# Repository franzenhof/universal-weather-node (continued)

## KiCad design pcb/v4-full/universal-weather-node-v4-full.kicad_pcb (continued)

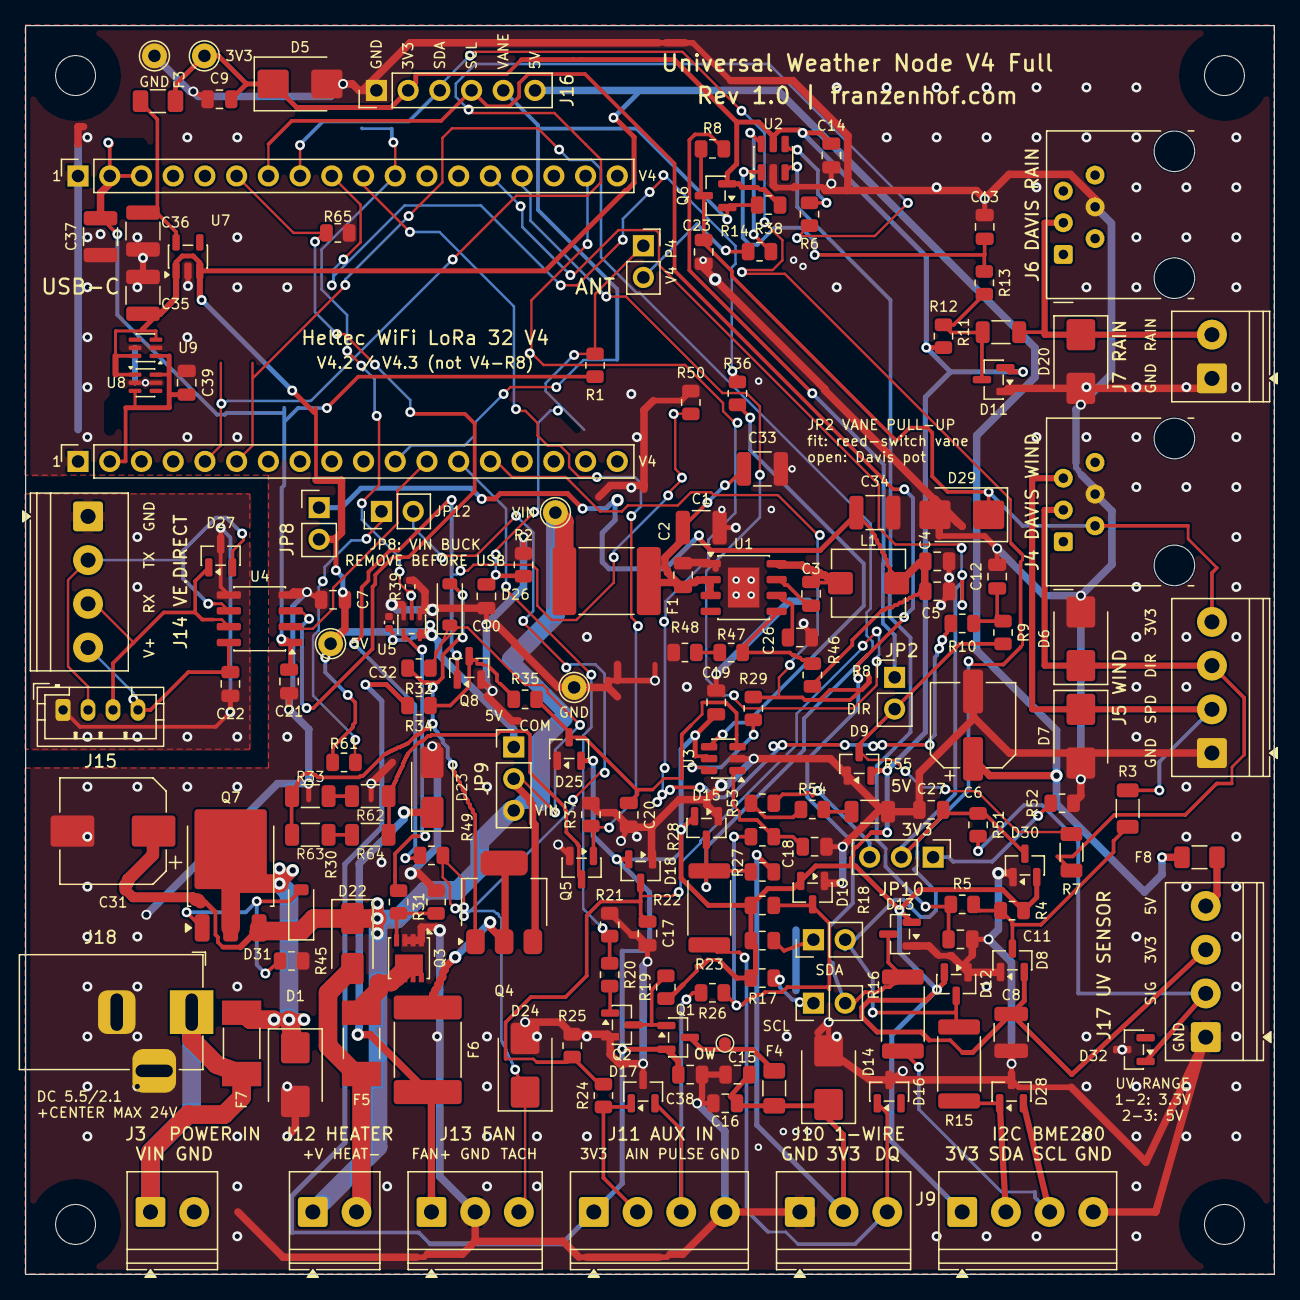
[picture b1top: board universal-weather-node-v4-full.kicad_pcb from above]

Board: 2 copper layers, 100.0 x 100.0 mm, 176 parts (1 on the bottom side), 88 nets.

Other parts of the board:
H1, H2, H3, H4: M3; MountingHole_3.2mm_M3

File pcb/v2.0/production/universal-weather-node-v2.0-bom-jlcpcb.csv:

"Comment","Designator","Footprint","LCSC Part #","MPN"
"10uF 50V","C1,C8,C33,C35,C36","Capacitor_SMD:C_1210_3225Metric","C77102","Murata GRM32ER71H106KA12L (10 uF, 50 V, X7R, 1210)"
"220nF 100V","C2","Capacitor_SMD:C_0805_2012Metric","C513710","Yageo CC0805KKX7R0BB224"
"100nF","C3,C7,C9,C10,C11,C14,C16,C17,C18,C19,C20,C21,C22,C23,C27","Capacitor_SMD:C_0805_2012Metric","C49678","Yageo CC0805KRX7R9BB104"
"22uF 25V","C4,C5,C38","Capacitor_SMD:C_0805_2012Metric","C45783","Samsung CL21A226MAQNNNE (22 uF, 25 V, X5R, 0805; basic)"
"100uF","C6","Capacitor_SMD:CP_Elec_6.3x7.7","C970685","DMBJ RVT1E101M0607 (25V)"
"1uF 50V","C12,C13,C15,C26,C39","Capacitor_SMD:C_0805_2012Metric","C28323","Samsung CL21B105KBFNNNE (1 uF 50 V X7R)"
"47uF 63V","C31","Capacitor_SMD:CP_Elec_8x10","C445452","Nichicon UCD1J470MNL1GS (47 uF, 63 V, SMD 8x10 mm)"
"100nF","C32","Capacitor_SMD:C_0402_1005Metric","C1525","Samsung CL05B104KO5NNNC (100 nF, 16 V, X7R, 0402)"
"22uF 25V","C34,C37","Capacitor_SMD:C_1210_3225Metric","C21397","Murata GRM32ER71E226KE15L (22 uF, 25 V, X7R, 1210)"
"SMBJ30CA","D1","Diode_SMD:D_SMB","C83847","Littelfuse SMBJ30CA"
"SMLVT3V3","D5,D6,D7,D14,D20,D29","Diode_SMD:D_SMB","C283619","SMLVT3V3"
"BAT54S","D8,D9,D11,D12,D13,D15,D18,D19,D25,D30","Package_TO_SOT_SMD:SOT-23","C7420333","R+O BAT54S (series pair, SOT-23; preferred extended)"
"PESD5V0S2BT","D16,D17,D27,D28,D32","Package_TO_SOT_SMD:SOT-23","C49338","Nexperia PESD5V0S2BT,215"
"SS210","D22,D23","Diode_SMD:D_SMA","C14996","SS210 (2 A, 100 V Schottky, SMA; basic)"
"SMBJ33A","D24","Diode_SMD:D_SMB","C19077586","SMBJ33A (33 V standoff, unidirectional, SMB; preferred extended)"
"BZT52C12","D26,D31","Diode_SMD:D_SOD-123","C19077410","BZT52C12 (12 V zener, SOD-123; preferred extended)"
"PTC 1.5A 60V","F1,F6","Fuse:Fuse_2920_7451Metric","C19078738","LUTE 2920L150/60GR (1.5 A hold, 60 V)"
"PTC 0.25A","F3","Fuse:Fuse_1206_3216Metric","C70068","nSMD025 (16V)"
"PTC 0.1A","F4,F8","Fuse:Fuse_1206_3216Metric","C70065","nSMD010 (60V)"
"4A 250V","F5","Fuse:Fuse_Littelfuse-NANO2-451_453","C19712551","SETsafe SCT6125T4A250V (4 A, 250 V)"
"6.3A 125V","F7","Fuse:Fuse_Littelfuse-NANO2-451_453","C178982","Littelfuse 045106.3MRL (6.3 A, 125 VDC)"
"10uH","L1","Inductor_SMD:L_Bourns_SRP5030T","C189932","Bourns SRP5030T-100M"
"AO3401A","Q1,Q6","Package_TO_SOT_SMD:SOT-23","C15127","AO3401A"
"AO3400A","Q2","Package_TO_SOT_SMD:SOT-23","C20917","AOS AO3400A"
"AON7264E","Q3","Package_SO:Vishay_PowerPAK_1212-8_Single","C431191","AOS AON7264E (60 V N-MOSFET, DFN 3.3x3.3)"
"DMP6023LE","Q4","Package_TO_SOT_SMD:SOT-223-3_TabPin2","C154901","Diodes Incorporated DMP6023LE-13"
"AO3422","Q5","Package_TO_SOT_SMD:SOT-23","C37130","AOS AO3422 (55 V N-MOSFET)"
"NCE60P50K","Q7","Package_TO_SOT_SMD:TO-252-3_TabPin2","C130104","NCE Power NCE60P50K"
"MMBT3904","Q8","Package_TO_SOT_SMD:SOT-23","C20526","Jiangsu Changjing MMBT3904(RANGE:100-300)"
"1M","R1,R2","Resistor_SMD:R_0805_2012Metric","C17514","UniOhm 0805W8F1004T5E"
"330","R3,R7,R11,R55","Resistor_SMD:R_1206_3216Metric","C17930","UniOhm 1206W4F3300T5E (1206, 0.25 W)"
"4.7k","R4,R5,R8,R12,R17,R18,R22,R27,R28,R35,R54","Resistor_SMD:R_0805_2012Metric","C17673","UniOhm 0805W8F4701T5E"
"1k","R6,R10,R14,R20,R29,R36","Resistor_SMD:R_0805_2012Metric","C17513","UniOhm 0805W8F1001T5E"
"10k","R9,R13,R21,R24,R34,R47,R51,R53,R61","Resistor_SMD:R_0805_2012Metric","C17414","UniOhm 0805W8F1002T5E"
"33 1W","R15,R16,R23","Resistor_SMD:R_2512_6332Metric","C53728","UniOhm 25121WF330JT4E (2512, 1 W)"
"47k","R19,R46,R49","Resistor_SMD:R_0805_2012Metric","C17713","UniOhm 0805W8F4702T5E"
"220","R26,R30","Resistor_SMD:R_0805_2012Metric","C17557","UniOhm 0805W8F2200T5E"
"100k","R31,R37,R38,R45,R50,R52,R65","Resistor_SMD:R_0805_2012Metric","C149504","UniOhm 0805W8F1003T5E"
"75k","R32","Resistor_SMD:R_0805_2012Metric","C17819","UNI-ROYAL 0805W8F7502T5E (75 kOhm, 1%, 0.125 W, 0805)"
"2k","R33,R62,R63,R64","Resistor_SMD:R_1206_3216Metric","C17944","UNI-ROYAL 1206W4F2001T5E (2 kOhm, 1%, 0.25 W, 1206)"
"100k","R39","Resistor_SMD:R_0402_1005Metric","C25741","UniOhm 0402WGF1003TCE"
"1.8k","R48","Resistor_SMD:R_0805_2012Metric","C17398","Uniroyal 0805W8F1801T5E"
"LMR36520ADDAR","U1","Package_SO:SOIC-8-1EP_3.9x4.9mm_P1.27mm_EP2.514x3.2mm","C2879422","TI LMR36520ADDAR"
"SN74LVC2G14DBVR","U2,U3","Package_TO_SOT_SMD:SOT-23-6","C5375976","UMW SN74LVC2G14DBVR (second source; TI C12401 had 33 in stock on 2026-11-21)"
"ADuM121N1BRZ","U4","Package_SO:SOIC-8_3.9x4.9mm_P1.27mm","C190783","ADUM121N1BRZ-RL7 (alt. ISO7721DR C366164)"
"SN74AHCT1G125DCKR","U5","Package_TO_SOT_SMD:SOT-353_SC-70-5","C350557","TI SN74AHCT1G125DCKR (SC-70-5)"
"AP2112K-3.3TRG1","U7","Package_TO_SOT_SMD:SOT-23-5","C51118","Diodes AP2112K-3.3TRG1 (600 mA LDO, SOT-23-5)"
"LM66100DCKR","U8,U9","Package_TO_SOT_SMD:SOT-363_SC-70-6","C2869734","TI LM66100DCKR (ideal diode 1.5 A, 79 mOhm, SC-70-6)"

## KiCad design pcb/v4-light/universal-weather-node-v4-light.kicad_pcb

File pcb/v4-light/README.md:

# Weather Node V4 Light Rev 1.0 (Heltec V4, through-hole)

A hand-solderable, low-cost board for the **Heltec WiFi LoRa 32 V4** (V4.2 / V4.3, not V4-R8).
All parts are through-hole except the TVS diodes: six SMB (large pads, easy to solder by hand) and
two optional PESD5V0S2BT in SOT-23.
It carries the core functions of the **V4 Full** with the **same GPIOs and the same signal
conditioning**:

| Function | Connector | V4 GPIO |
|----------|-----------|---------|
| Davis wind speed / direction | J4 RJ11 + J5 screw terminal (GND, SPD, DIR, 3V3) | 44 / 6 (ADC1) |
| Wind-vane supply (switched, LOW = on) | J4 pin 2 / J5 3V3 | 34 |
| Davis rain | J6 RJ11 + J7 screw terminal (GND, RAIN) | 16 (P4) |
| BME280 (I²C) | J8 (3V3, SDA, SCL, GND) | 41 / 42 |
| DS18B20 (1-Wire), switched supply (HIGH = on) | J9 (GND, 3V3, DQ) | 43 / 47 |
| Hardware revision ID | – | 15 (P4) |

**Power:** the board has no power input of its own. Power and flash the module through its
**USB-C** connector (V4 header pin 2 = USB VBUS stays open, so there is no back-feeding).
The sensors run from the module's 3.3 V through a 170 mA PTC (F1); the 1-Wire supply has its
own 100 mA PTC (F2).

**Not on the V4 Light** (V4 Full only): VIN 6–29 V supply, heater and fan outputs, fan tacho,
AUX inputs, UV input, VE.Direct.

**Board:** 100 × 80 mm, 2 layers, four M3 holes on a 66 × 72 mm pattern (centres 30/96 mm from the
left edge, 4/76 mm from the top). The V4 stands at the left edge, USB-C flush with the top edge.
71 parts (2 of them optional), see the [BOM](production/universal-weather-node-v4-light-bom.csv).

## Protection and conditioning

- **SMB TVS SMLVT3V3** at wind speed, wind direction, rain (between each jack and its terminal),
  the switched vane supply, the 1-Wire supply and the 3.3 V sensor rail.
- **Resistors on a 10.16 mm (400 mil) pitch** like Rev 1.3: room for Vishay PR01 (1 W, 6.5 × 2.5 mm)
  as well as ordinary 0207 / 0204 metal-film parts.
- **330 Ω** series resistors (Davis lines), **100 Ω** (I²C, 1-Wire DQ), **BAT43** clamps to 3.3 V
  and GND on every input.
- **PESD5V0S2BT** (low-capacitance dual ESD TVS, SOT-23) directly at J8 (SDA, SCL) and J9 (DQ) —
  **optional**: leave them out if SOT-23 is too fiddly, the 100 Ω + BAT43 into the TVS-protected
  3.3 V rail remain. An SMB TVS is not used there because its capacitance would load the buses.
- **Mounting holes plated and on GND:** screwed to a grounded metal plate or enclosure, ESD
  discharges take the short way to ground instead of crossing the board.
- RC filters as on the V4 Full (wind speed 4.7k/100 nF, direction 10k/1 µF, rain 10k/1 µF) and a
  **74HC14** (DIP-14) inverting Schmitt trigger for wind speed and rain — the same polarity as the
  V4 Full's 74LVC2G14, so the firmware counts identically.
- JP1: 4.7k pull-up for reed-switch vanes (open for the Davis potentiometer). JP2/JP3: extra 4.7k
  I²C pull-ups for cables longer than 0.5 m.

## Silkscreen

Verbose on purpose: every part carries its value on the front (inside the body outline where it is
free of pads, otherwise beside it — only C3 is printed in the back BOM alone), FET type
(P-FET / N-FET) next to Q1–Q3, terminal pin names, jumper functions. The back carries the complete
BOM grouped by value (resistors, capacitors / fuses, diodes / FET / IC, connectors), the connector
pinouts by pin number, jumpers and GPIOs, and polarity / assembly-order notes
(`tools/pcbgen/light_silk.py`).

## Revision ID and firmware

R1/R2 = 1 MΩ / 470 kΩ put **0.32 × 3.3 V ≈ 1.06 V** on GPIO15 (V4 Full: 1 MΩ / 1 MΩ ≈ 1.65 V,
accepted window 1.30–2.00 V). The firmware (4.x) accepts **0.85–1.25 V as V4 Light** (`pcbRev` 21;
V4 Full stays 20), logs `HW revision ID (GPIO15): … mV -> PCB V4 Light` and offers only the
functions above: heater, fan, tacho, AUX, second wind sensor, UV and VE.Direct are hidden in the
web settings and refused by downlink/MQTT, and their GPIOs are never driven.

## Assembly

1. SMD first: the SMB TVS diodes (band = cathode = pad 1 on the signal side) and, if fitted,
   D19/D20 (PESD5V0S2BT, SOT-23); then the low parts
   (resistors, BAT43 — band = cathode, ceramic capacitors), DIP socket, TO-92, PTCs, C2 (+ = square pad),
   headers, terminals and RJ11 jacks, the Heltec sockets last. The TVS diodes sit 3–5 mm clear of the RJ11 jacks and screw terminals,
   so they can still be soldered if the jacks went in first.
2. **Q1/Q2 (LP0701N3-G) and Q3 (TN2106N3-G) are S-G-D in TO-92 (N3)** (datasheets checked; the SOT-23 versions K1/LG differ) — check the flat side against the
   silkscreen outline.
3. **J3 (P4 socket, GPIO15/16) sits 0.45 mm off the 2.54 mm grid** (position from Heltec's V4 3D model):
   check it with a real V4 before soldering the sockets. Solder J1/J2/J3 with the module plugged in.

## Status

Generated with `tools/pcbgen` (`design_light.py`, `schem_light.py`, `layout_light.py`, then
`light_silk.py` for the verbose silkscreen): ERC 0, DRC 0 errors / 0 unconnected, schematic parity OK;
remaining warnings are silkscreen overlaps (value texts touching outlines) and clipped silk at pads.
**Not yet built or tested.**

```bash
mkdir -p proj && cp pcb/v4-light/universal-weather-node-v4-light.kicad_pro proj/
DESIGN=design_light SCHEM=schem_light LAYOUT=layout_light N=universal-weather-node-v4-light \
  OUT=$PWD/proj/out ATTEMPTS=8 bash tools/pcbgen/build2.sh $PWD/proj
LAYOUT=layout_light <KiCad python> tools/pcbgen/light_silk.py proj/universal-weather-node-v4-light.kicad_pcb
bash tools/pcbgen/export_light.sh pcb/v4-light     # after copying the result to pcb/v4-light
```

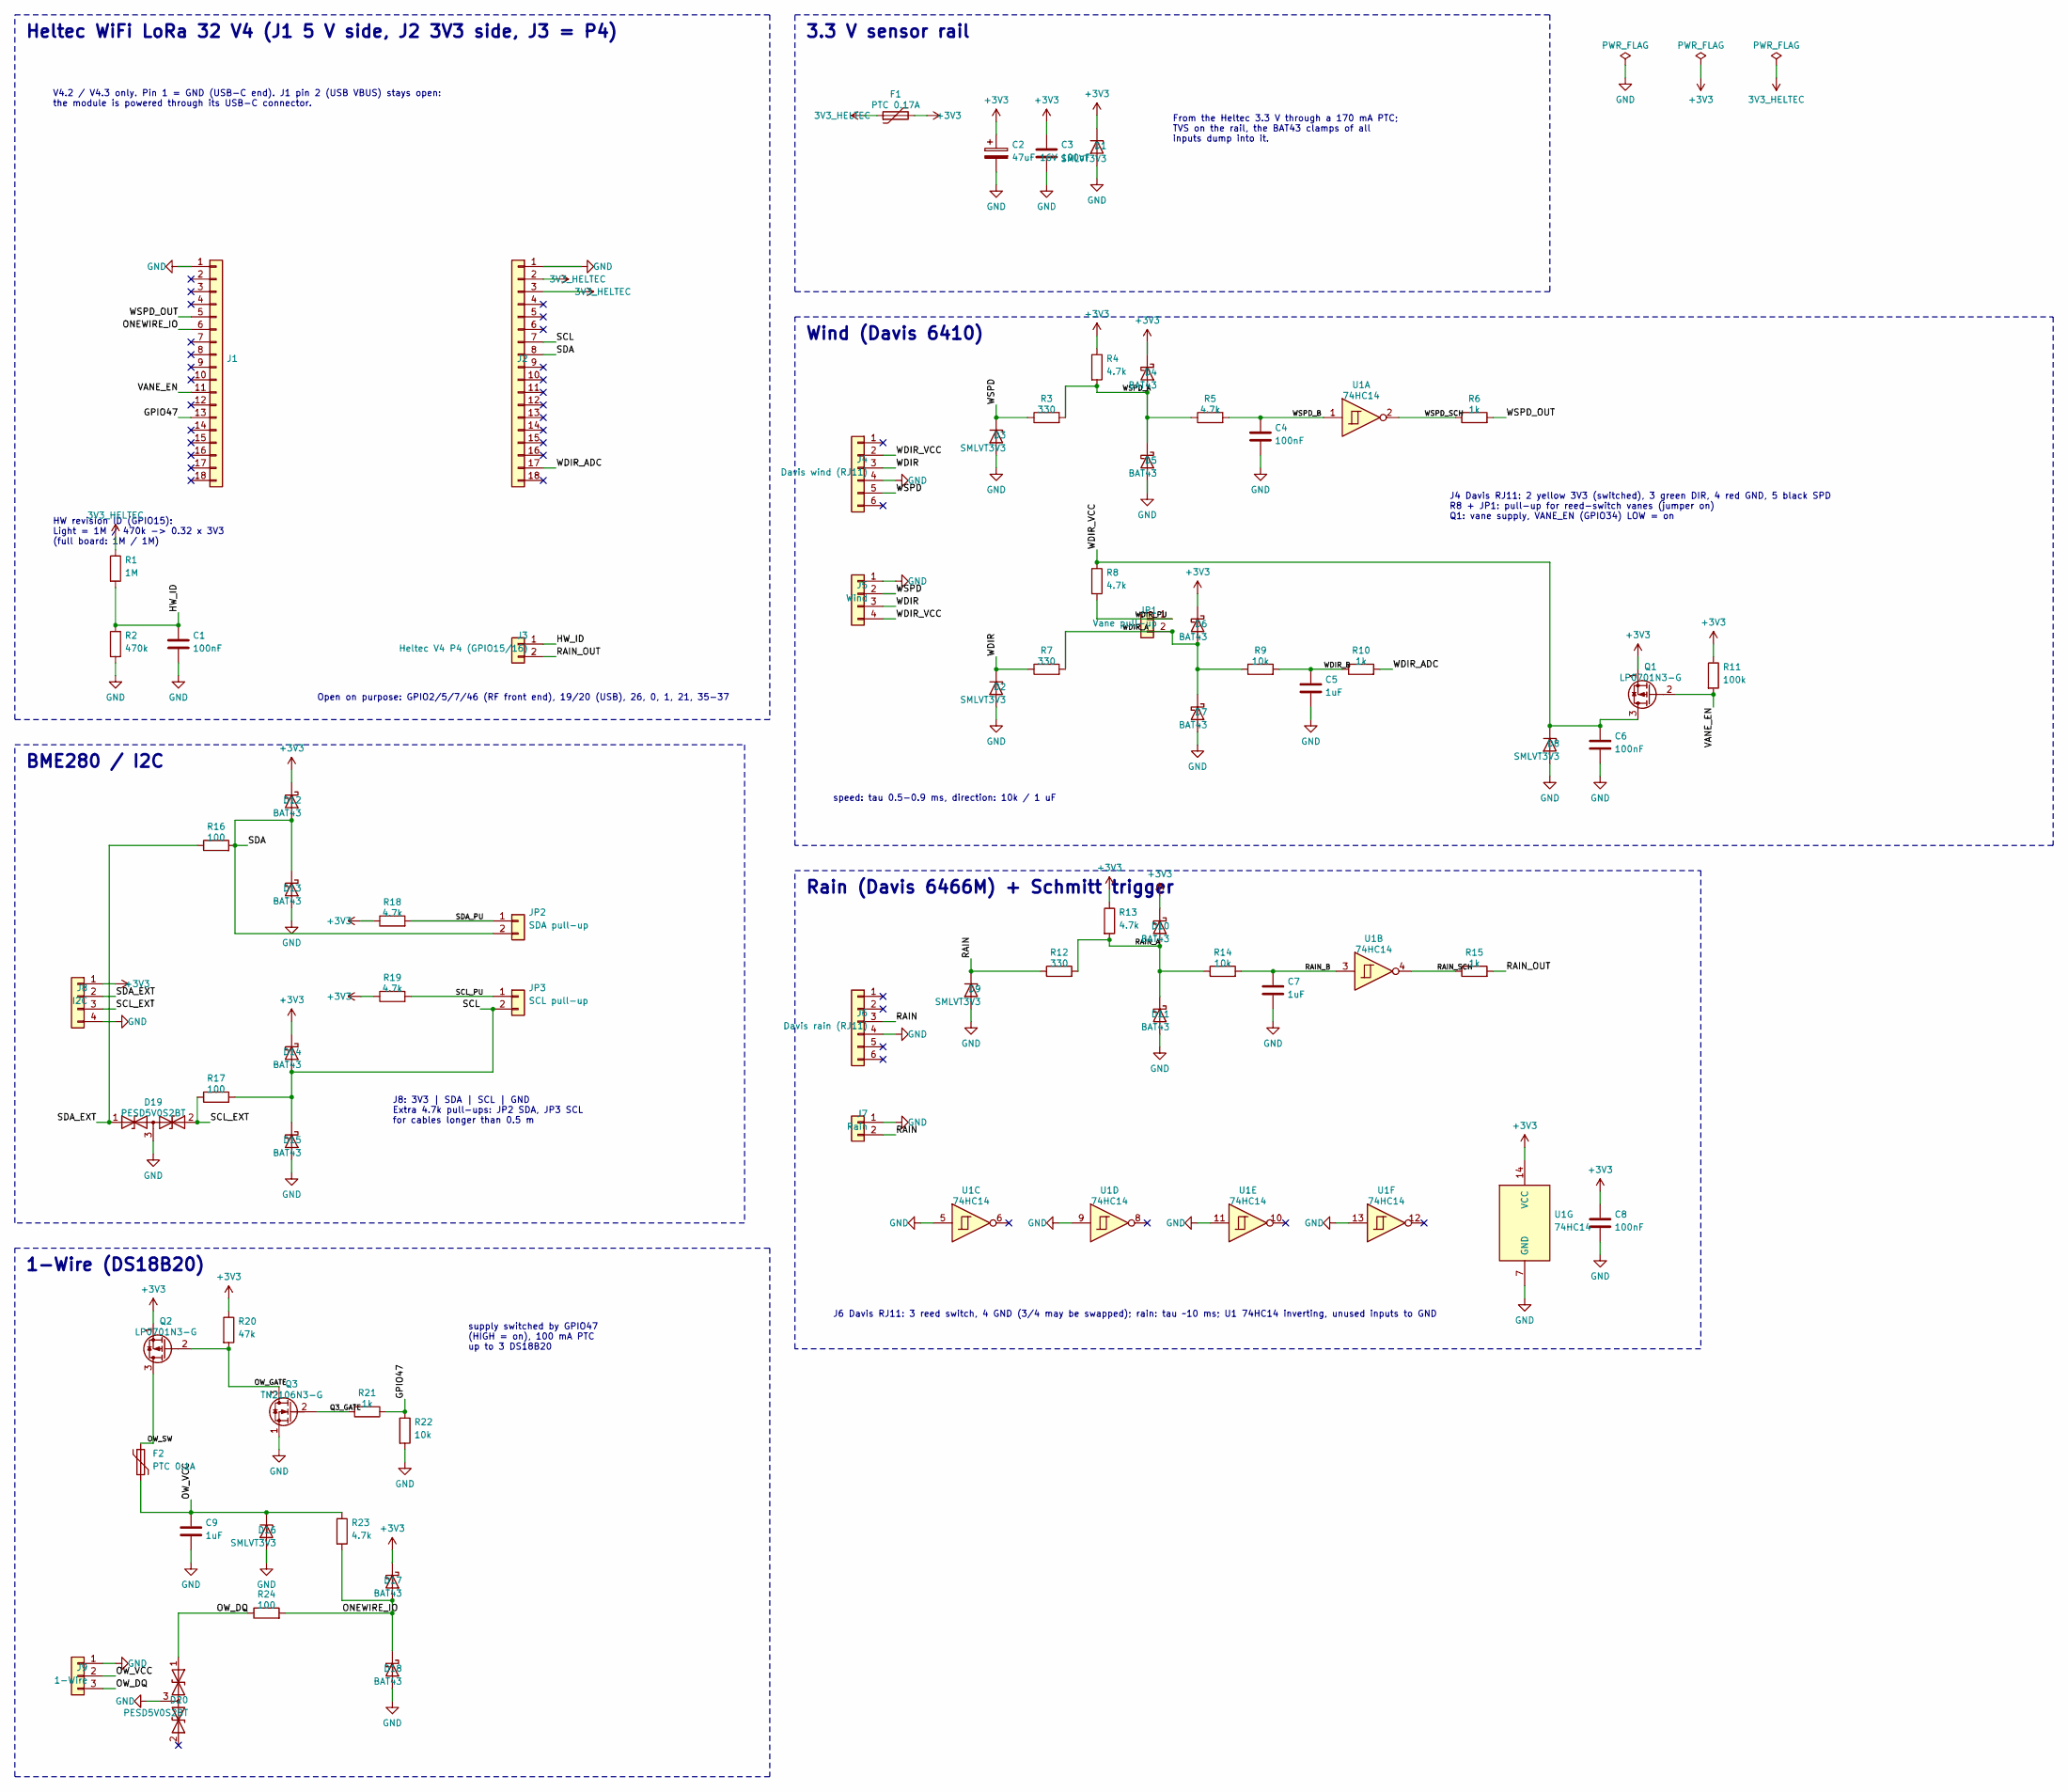
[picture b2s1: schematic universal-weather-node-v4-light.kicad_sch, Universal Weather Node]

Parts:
C1, C3, C4, C6, C8: 100nF; C_Disc_D3.8mm_W2.6mm_P2.50mm
C2: 47uF 16V; CP_Radial_D5.0mm_P2.00mm
C5, C7, C9: 1uF; C_Disc_D3.8mm_W2.6mm_P2.50mm
D1, D2, D3, D8, D9, D16: SMLVT3V3; D_SMB
D4, D5, D6, D7, D10, D11, D12, D13, D14, D15, D17, D18: BAT43; D_DO-35_SOD27_P7.62mm_Horizontal
D19, D20: PESD5V0S2BT; SOT-23
F1: PTC 0.17A; C_Disc_D7.5mm_W2.5mm_P5.00mm
F2: PTC 0.1A; C_Disc_D7.5mm_W2.5mm_P5.00mm
J1: Heltec V4 header (5V side); PinSocket_1x18_P2.54mm_Vertical
J2: Heltec V4 header (3V3 side); PinSocket_1x18_P2.54mm_Vertical
J3: Heltec V4 P4 (GPIO15/16); PinSocket_1x02_P2.54mm_Vertical
J4: Davis wind (RJ11); RJ12_Amphenol_54601-x06_Horizontal
J5: Wind; TerminalBlock_Phoenix_PT-1,5-4-3.5-H_1x04_P3.50mm_Horizontal
J6: Davis rain (RJ11); RJ12_Amphenol_54601-x06_Horizontal
J7: Rain; TerminalBlock_Phoenix_PT-1,5-2-3.5-H_1x02_P3.50mm_Horizontal
J8: I2C; TerminalBlock_Phoenix_PT-1,5-4-3.5-H_1x04_P3.50mm_Horizontal
J9: 1-Wire; TerminalBlock_Phoenix_PT-1,5-3-3.5-H_1x03_P3.50mm_Horizontal
JP1: Vane pull-up; PinHeader_1x02_P2.54mm_Vertical
JP2: SDA pull-up; PinHeader_1x02_P2.54mm_Vertical
JP3: SCL pull-up; PinHeader_1x02_P2.54mm_Vertical
Q1, Q2: LP0701N3-G; TO-92_Inline_Wide
Q3: TN2106N3-G; TO-92_Inline_Wide
R1: 1M; R_Axial_DIN0207_L6.3mm_D2.5mm_P10.16mm_Horizontal
R2: 470k; R_Axial_DIN0207_L6.3mm_D2.5mm_P10.16mm_Horizontal
R3, R7, R12: 330; R_Axial_DIN0207_L6.3mm_D2.5mm_P10.16mm_Horizontal
R4, R5, R8, R13, R18, R19, R23: 4.7k; R_Axial_DIN0207_L6.3mm_D2.5mm_P10.16mm_Horizontal
R6, R10, R15, R21: 1k; R_Axial_DIN0207_L6.3mm_D2.5mm_P10.16mm_Horizontal
R9, R14, R22: 10k; R_Axial_DIN0207_L6.3mm_D2.5mm_P10.16mm_Horizontal
R11: 100k; R_Axial_DIN0207_L6.3mm_D2.5mm_P10.16mm_Horizontal
R16, R17, R24: 100; R_Axial_DIN0207_L6.3mm_D2.5mm_P10.16mm_Horizontal
R20: 47k; R_Axial_DIN0207_L6.3mm_D2.5mm_P10.16mm_Horizontal
U1: 74HC14; DIP-14_W7.62mm

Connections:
3V3_HELTEC: F1.1, J2.2, J2.3, R1.1
+3V3: C2.1, C3.1, C8.1, D1.1 (K), D4.1 (K), D6.1 (K), D10.1 (K), D12.1 (K), D14.1 (K), D17.1 (K), F1.2, J8.1, Q1.1 (S), Q2.1 (S), R4.1, R11.1, R13.1, R18.1, R19.1, R20.1, U1.14 (VCC)
/GPIO47: J1.13, R21.1, R22.1
/HW_ID: C1.1, J3.1, R1.2, R2.1
/ONEWIRE_IO: D17.2 (A), D18.1 (K), J1.6, R23.2, R24.2
/OW_DQ: D20.1 (A1), J9.3, R24.1
/OW_GATE: Q2.2 (G), Q3.3 (D), R20.2
/OW_SW: F2.1, Q2.3 (D)
/OW_VCC: C9.1, D16.1 (K), F2.2, J9.2, R23.1
/Q3_GATE: Q3.2 (G), R21.2
/RAIN: D9.1 (K), J6.3, J7.2, R12.1
/RAIN_A: D10.2 (A), D11.1 (K), R12.2, R13.2, R14.1
/RAIN_B: C7.1, R14.2, U1.3
/RAIN_OUT: J3.2, R15.2
/RAIN_SCH: R15.1, U1.4
/SCL: D14.2 (A), D15.1 (K), J2.7, JP3.2, R17.2
/SCL_EXT: D19.2 (A2), J8.3, R17.1
/SCL_PU: JP3.1, R19.2
/SDA: D12.2 (A), D13.1 (K), J2.8, JP2.2, R16.2
/SDA_EXT: D19.1 (A1), J8.2, R16.1
/SDA_PU: JP2.1, R18.2
/VANE_EN: J1.11, Q1.2 (G), R11.2
/WDIR: D2.1 (K), J4.3, J5.3, R7.1
/WDIR_A: D6.2 (A), D7.1 (K), JP1.2, R7.2, R9.1
/WDIR_ADC: J2.17, R10.2
/WDIR_B: C5.1, R9.2, R10.1
/WDIR_PU: JP1.1, R8.2
/WDIR_VCC: C6.1, D8.1 (K), J4.2, J5.4, Q1.3 (D), R8.1
/WSPD: D3.1 (K), J4.5, J5.2, R3.1
/WSPD_A: D4.2 (A), D5.1 (K), R3.2, R4.2, R5.1
/WSPD_B: C4.1, R5.2, U1.1
/WSPD_OUT: J1.5, R6.2
/WSPD_SCH: R6.1, U1.2
GND: C1.2, C2.2, C3.2, C4.2, C5.2, C6.2, C7.2, C8.2, C9.2, D1.2 (A), D2.2 (A), D3.2 (A), D5.2 (A), D7.2 (A), D8.2 (A), D9.2 (A), D11.2 (A), D13.2 (A), D15.2 (A), D16.2 (A), D18.2 (A), D19.3 (common), D20.3 (common), J1.1, J2.1, J4.4, J5.1, J6.4, J7.1, J8.4, J9.1, Q3.1 (S), R2.2, R22.2, U1.5, U1.7 (GND), U1.9, U1.11, U1.13; also elsewhere on the board

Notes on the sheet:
Heltec WiFi LoRa 32 V4 (J1 5 V side, J2 3V3 side, J3 = P4)
V4.2 / V4.3 only. Pin 1 = GND (USB-C end). J1 pin 2 (USB VBUS) stays open: the module is powered through its USB-C connector.
HW revision ID (GPIO15): Light = 1M / 470k -> 0.32 x 3V3 (full board: 1M / 1M)
Open on purpose: GPIO2/5/7/46 (RF front end), 19/20 (USB), 26, 0, 1, 21, 35-37
3.3 V sensor rail
From the Heltec 3.3 V through a 170 mA PTC; TVS on the rail, the BAT43 clamps of all inputs dump into it.
Wind (Davis 6410)
J4 Davis RJ11: 2 yellow 3V3 (switched), 3 green DIR, 4 red GND, 5 black SPD R8 + JP1: pull-up for reed-switch vanes (jumper on) Q1: vane supply, VANE_EN (GPIO34) LOW = on
speed: tau 0.5-0.9 ms, direction: 10k / 1 uF
Rain (Davis 6466M) + Schmitt trigger
J6 Davis RJ11: 3 reed switch, 4 GND (3/4 may be swapped); rain: tau ~10 ms; U1 74HC14 inverting, unused inputs to GND
BME280 / I2C
J8: 3V3 | SDA | SCL | GND Extra 4.7k pull-ups: JP2 SDA, JP3 SCL for cables longer than 0.5 m
1-Wire (DS18B20)
supply switched by GPIO47 (HIGH = on), 100 mA PTC up to 3 DS18B20

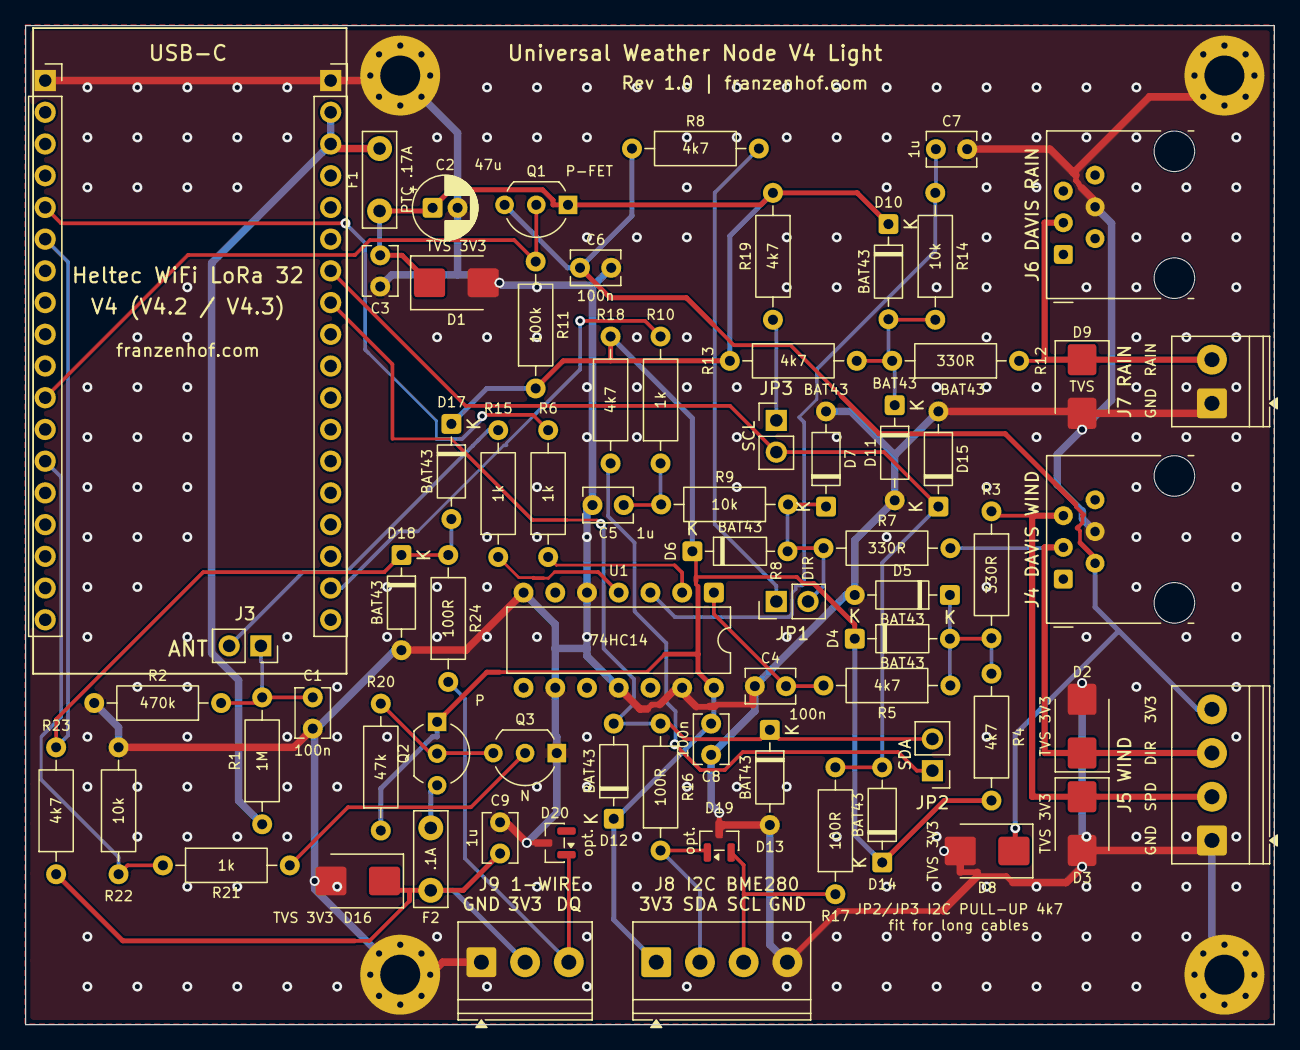
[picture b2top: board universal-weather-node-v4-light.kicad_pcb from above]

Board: 2 copper layers, 100.0 x 80.0 mm, 75 parts (0 on the bottom side), 34 nets.

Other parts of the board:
H1, H2, H3, H4: M3; MountingHole_3.2mm_M3_Pad_Via

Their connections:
GND: H1.1, H2.1, H3.1, H4.1; also elsewhere on the board

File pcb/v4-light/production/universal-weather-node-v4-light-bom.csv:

References,Qty,Value,Part / order hint,Footprint,Note
C1 C3 C4 C6 C8,5,100nF,"ceramic 100 nF 50 V X7R, 2.5 mm pitch",C_Disc_D3.8mm_W2.6mm_P2.50mm,
C2,1,47uF 16V,"electrolytic 47 uF >= 16 V, radial 5 mm, 2 mm pitch",CP_Radial_D5.0mm_P2.00mm,polarised: + = square pad
C5 C7 C9,3,1uF,"ceramic 1 uF 50 V X7R, 2.5 mm pitch",C_Disc_D3.8mm_W2.6mm_P2.50mm,
D1 D2 D3 D8 D9 D16,6,SMLVT3V3,"ST SMLVT3V3 TVS 3.3 V, SMB (DO-214AA)",D_SMB,SMD; cathode band = pad 1 (signal side)
D4 D5 D6 D7 D10 D11 D12 D13 D14 D15 D17 D18,12,BAT43,"BAT43 Schottky, DO-35",D_DO-35_SOD27_P7.62mm_Horizontal,band = cathode
D19 D20,2,PESD5V0S2BT,"Nexperia PESD5V0S2BT dual ESD TVS, SOT-23",SOT-23,"optional (may be left out); low capacitance, I2C / 1-Wire DQ"
F1,1,PTC 0.17A,"Littelfuse RXEF017 (radial PTC, 5.1 mm)",C_Disc_D7.5mm_W2.5mm_P5.00mm,
F2,1,PTC 0.1A,"Littelfuse RXEF010 (radial PTC, 5.1 mm)",C_Disc_D7.5mm_W2.5mm_P5.00mm,
J1 J2,2,Heltec V4 header (5V side),"1x18 female header 2.54 mm, 8.5 mm high (e.g. Kinghelm KH-2.54FH-1X18P-H8.5)",PinSocket_1x18_P2.54mm_Vertical,J1 + J2
J3,1,Heltec V4 P4 (GPIO15/16),"1x2 female header 2.54 mm, 8.5 mm high",PinSocket_1x02_P2.54mm_Vertical,check the position with the real V4
J4,1,Davis wind (RJ11),"RJ11/RJ12 6P6C jack, horizontal THT, unshielded (EVERCOM 5301-6P6C / Amphenol 54601-906)",RJ12_Amphenol_54601-x06_Horizontal,
J5,1,Wind,"terminal block 3.5 mm, 4-pole (e.g. DB125-3.5-4P / Phoenix PT 1,5/4-3,5-H)","TerminalBlock_Phoenix_PT-1,5-4-3.5-H_1x04_P3.50mm_Horizontal",
J6,1,Davis rain (RJ11),"RJ11/RJ12 6P6C jack, horizontal THT, unshielded (EVERCOM 5301-6P6C / Amphenol 54601-906)",RJ12_Amphenol_54601-x06_Horizontal,
J7,1,Rain,"terminal block 3.5 mm, 2-pole (e.g. DB125-3.5-2P / Phoenix PT 1,5/2-3,5-H)","TerminalBlock_Phoenix_PT-1,5-2-3.5-H_1x02_P3.50mm_Horizontal",
J8,1,I2C,"terminal block 3.5 mm, 4-pole","TerminalBlock_Phoenix_PT-1,5-4-3.5-H_1x04_P3.50mm_Horizontal",
J9,1,1-Wire,"terminal block 3.5 mm, 3-pole (e.g. DB125-3.5-3P / Phoenix PT 1,5/3-3,5-H)","TerminalBlock_Phoenix_PT-1,5-3-3.5-H_1x03_P3.50mm_Horizontal",
JP1,1,Vane pull-up,"pin header 1x2, 2.54 mm + jumper",PinHeader_1x02_P2.54mm_Vertical,fit only for reed-switch vanes
JP2,1,SDA pull-up,"pin header 1x2, 2.54 mm + jumper",PinHeader_1x02_P2.54mm_Vertical,fit for long I2C cables
JP3,1,SCL pull-up,"pin header 1x2, 2.54 mm + jumper",PinHeader_1x02_P2.54mm_Vertical,fit for long I2C cables
Q1 Q2,2,LP0701N3-G,"Microchip LP0701N3-G P-MOSFET, TO-92",TO-92_Inline_Wide,pinout S-G-D: check the flat side against the silkscreen
Q3,1,TN2106N3-G,"Microchip TN2106N3-G N-MOSFET, TO-92",TO-92_Inline_Wide,pinout S-G-D
R1,1,1M,"resistor 1M Ohm, metal film 0.6 W 1 %, 0207 (10.16 mm pitch)",R_Axial_DIN0207_L6.3mm_D2.5mm_P10.16mm_Horizontal,
R2,1,470k,"resistor 470k Ohm, metal film 0.6 W 1 %, 0207 (10.16 mm pitch)",R_Axial_DIN0207_L6.3mm_D2.5mm_P10.16mm_Horizontal,
R3 R7 R12,3,330,"resistor 330 Ohm, Vishay PR01 1 W (e.g. PR01000103300JA100) or metal film 0.6 W 1 %, 0207 (10.16 mm pitch)",R_Axial_DIN0207_L6.3mm_D2.5mm_P10.16mm_Horizontal,surge series resistor: pulse-rated PR01 preferred (as Rev 1.3)
R4 R5 R8 R13 R18 R19 R23,7,4.7k,"resistor 4.7k Ohm, metal film 0.6 W 1 %, 0207 (10.16 mm pitch)",R_Axial_DIN0207_L6.3mm_D2.5mm_P10.16mm_Horizontal,
R6 R10 R15 R21,4,1k,"resistor 1k Ohm, metal film 0.6 W 1 %, 0207 (10.16 mm pitch)",R_Axial_DIN0207_L6.3mm_D2.5mm_P10.16mm_Horizontal,
R9 R14 R22,3,10k,"resistor 10k Ohm, metal film 0.6 W 1 %, 0207 (10.16 mm pitch)",R_Axial_DIN0207_L6.3mm_D2.5mm_P10.16mm_Horizontal,
R11,1,100k,"resistor 100k Ohm, metal film 0.6 W 1 %, 0207 (10.16 mm pitch)",R_Axial_DIN0207_L6.3mm_D2.5mm_P10.16mm_Horizontal,
R16 R17 R24,3,100,"resistor 100 Ohm, Vishay PR01 1 W (e.g. PR01000101000JA100) or metal film 0.6 W 1 %, 0207 (10.16 mm pitch)",R_Axial_DIN0207_L6.3mm_D2.5mm_P10.16mm_Horizontal,surge series resistor: pulse-rated PR01 preferred (as Rev 1.3)
R20,1,47k,"resistor 47k Ohm, metal film 0.6 W 1 %, 0207 (10.16 mm pitch)",R_Axial_DIN0207_L6.3mm_D2.5mm_P10.16mm_Horizontal,
U1,1,74HC14,SN74HC14N (DIP-14) + DIP-14 socket,DIP-14_W7.62mm,notch = pin 1
,1,Heltec WiFi LoRa 32 V4,"Heltec WiFi LoRa 32 V4 (V4.2 / V4.3, not V4-R8)",,on J1/J2/J3

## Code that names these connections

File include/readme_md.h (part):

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Prototype reverse-polarity tests are still required.

USB powers the Heltec, the 3.3 V sensor rail (via U7 from the module's 5 V pin), UV and other measurement interfaces.
A 5 V fan is possible with JP9 pins 1–2, subject to the **combined USB and
Heltec-path current budget**, not a guaranteed additional 0.5 A. The 250 mA
sensor PTC is not a guarantee of available Heltec regulator current.
USB does not power the VIN rail: the heater and a VIN-mode fan require VIN.
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| DS18B20 / powered 3-wire 1-Wire (J10) | Yes, within sensor supply budget | Yes, within sensor supply budget |
| AUX analog / pulse inputs (J11) | Yes; 3.3 V sensor supply available, observe input limits | Same |
| UV sensor (J17) | Yes; 3.3 V **or** 5 V supply available; set JP10 for signal range | Same |
| 5 V fan (J13), JP9 pins 1–2 | Possible within combined USB/cable/Heltec-path budget; **not a guaranteed extra 0.5 A** | Design target up to 0.5 A; shares buck capacity with Heltec/sensors |
| VIN-voltage fan (J13), JP9 pins 2–3 | **No load power** | Yes, design target up to 1 A; fan must tolerate actual VIN, including battery full-charge voltage |
| Heater (J12) | **No load power**, even though control electronics are powered | Yes, design target up to 3 A; heater voltage is protected VIN, **not regulated 5/12/24 V** |
| Fan tacho input (J13) | Input electronics work; a board-powered fan needs the 5 V selection above | Input electronics work with either fan-supply selection |
| Isolated VE.Direct (J14/J15) | Yes **if the Victron device powers the isolated side** | Same; VIN does not power the isolated side |
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100 Hz PWM edges/temperature. Fit **JP12** for the R61 10k pull-up to +5V
needed by open-collector PC fan tachometers. Remove JP12 for an externally
pulled-up or push-pull tacho, especially at 12/24 V, to avoid backfeeding +5V.
J13 retains its original pinout; this adds no separate four-wire fan PWM pin.

**Electrical-stability improvements (v2.0):**

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- **BAT54S clamps** (one SOT-23 per signal, replacing the BAT43 pairs) before the GPIO pins
- **RC low-pass filters** to debounce the reed switches — wind: 330 Ω + 4.7 kΩ + 100 nF (τ ≈ 0.5–0.9 ms, below the ~1.5 ms minimum contact time at full speed); rain: 330 Ω + 10 kΩ + 1 µF (τ ≈ 10–15 ms); wind direction: 10 kΩ + 1 µF
- **74LVC2G14 Schmitt trigger** on wind speed and rain (inverting, as Rev 1.3)
- **1-Wire supply** switched by GPIO47 (P-MOSFET), 100 mA PTC, 1 µF + 100 nF buffer; C38 (22 µF) at the switch input supplies the switch-on charge so the 3.3 V sensor rail barely dips
- **Extra I²C pull-ups** (4.7 kΩ) for BME280 cables up to 2 m — v2.0: two separate 2-pin headers, **JP1 = SDA** and **JP11 = SCL** (pins 1–2 on each). The rows are 5.08 mm apart, with one empty 2.54 mm grid row between them, preventing a normal 2.54 mm shunt from being fitted across the rows.

**New in v2.0:**

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- **Fan tacho** on GPIO40: transistor level conversion for an open-collector signal or an external pull-up, without feeding that voltage back into the 3.3 V rail; filter and Schmitt trigger follow the transistor
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| J3 POWER IN | 1 VIN · 2 GND | 6–29.2 V only; fit JP8 for VIN, remove before USB |
| J12 HEATER | 1 +V · 2 HEAT- | Load between +V and HEAT-, 3 A design target, runs at VIN voltage; HEAT- is switched, not permanent GND |
| J13 FAN | 1 FAN+ · 2 GND · 3 TACH | JP9 selects 5 V (0.5 A target) or protected VIN (1 A target); tacho input |
| J11 AUX IN | 1 3V3 · 2 AIN · 3 PULSE · 4 GND | Analog 0–3.3 V (GPIO4), or 0–5 V with R25 and matching scale; pulse/reed (GPIO48) |
| J10 1-WIRE | 1 GND · 2 3V3 · 3 DQ | DS18B20, three-wire powered bus; no parasite-power support |
| J9 I2C BME280 | 1 3V3 · 2 SDA · 3 SCL · 4 GND | 3.3 V BME280 at address 0x76 |

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| 5 | Black | Wind speed (reed switch → pulse counter) |
| 6 | – | n/c |

**Rain sensor (Davis 6466M) – RJ11 6-pin**

| Pin | Color | Function |
|-----|-------|----------|
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
- TVS diode (SMLVT3V3 / U4) added at the rain connector
- Second 1-Wire bus removed (the firmware uses only one bus on both revisions)
- Wind speed and rain moved from GPIO 3/4 to GPIO 6/7 (GPIO 3 is a strapping pin)
- 74LVC2G14 Schmitt trigger on wind speed and rain — it inverts, so the firmware counts falling edges on Rev 1.3
- 5 V input connects directly to the Heltec's 5 V pin (J2 pin 2)
- Optional footprint R21 (4.7 kΩ) for non-Davis wind vanes (see [Using Other Sensors](#using-other-sensors))
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| UV sensor, divider scale | GPIO3; terminal voltage per ADC voltage, matching JP10 (1–2: 0–3.3 V, 1.1; 2–3: 0–5 V, 1.66534) | off, 1.1 |
| UV index enabled, calibration verified | Index is reported only when both switches are on and calibration is valid | both off |
| UV index slope, offset | Linear conversion of terminal volts into index; slope 0.001–30 index/V, offset −10…+10 | 1.0, 0.0 (not calibrated) |
| AUX pulse counter | GPIO48 | off |
| 2nd wind sensor, vane offset | off / speed (anemometer at AUX `PULSE`) / speed + direction (vane at AUX `AIN`) — see [Second Wind Sensor](#second-wind-sensor-pcb-v20); takes over the AUX inputs it uses | off, 0° |
| Heater mode, power, thresholds | off / on / auto; auto: on below the switch-on temperature with the start power, rising linearly to full power at the full-power temperature | off, 100 %, 4.0 °C / 10 %, −10.0 °C / 100 % |
| Fan mode, speed, threshold, minimum PV power | off / on / auto (from the threshold); PWM 1–100 %; °C; W (VE.Direct, 0 = ignore) | off, 100 %, 15.0 °C, 0 |
| Fan tacho, pulses per revolution | GPIO40 | off, 2 |
| Victron VE.Direct | GPIO33/34 | off |
| Minimum battery voltage for heater/fan | V (VE.Direct), 0 = no limit | 0 |
| **Wi-Fi + MQTT** | | |
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- **Sub-samples** (gust, direction, BME280) run as before, every sample interval.
- **Wind-vane supply** (PCB v2.0): with **`vanePowerSave = 1`** (default) the potentiometer is only powered for ~100 ms around each reading (the filter, τ ≈ 15 ms, settles in that time, spent in light sleep). Set it to `0` for vanes that need continuous power.
- **VE.Direct:** the node stays awake for the last ~2.5 s before each uplink to catch a frame.
- Only active while **Wi-Fi is off** and neither heater nor fan is running (their PWM stops in light sleep). Wind, rain and AUX pulses (counter or 2nd anemometer) are counted while sleeping. The user button still wakes the node and turns the display on.
- The power saving still has to be measured on real hardware.

---
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| No measurements sent yet | Wait one cycle (default 300 s); check transport enable flags. An active portal pauses normal operation |
| LoRaWAN remains “not joined” | DevEUI/JoinEUI/AppKey, region, network profile and gateway coverage; inspect the logged error. Retries are spaced by at least 60 s |
| Uplinks arrive, command does not run | Queue HEX `03` on **FPort 1**, wait for the next uplink; inspect gateway TX_ACK and device logs. FPort 0 traffic is MAC control, not this command; this firmware uses Class A |
| Wind/rain stays at zero | Correct manual Rev 1.2/1.3 selection, sensor enabled, numbered pinout, reed contact; debug log shows pulse counts |
| BME280 missing | Actual BME280 (not BMP280), 3.3 V supply, address 0x76, SDA/SCL wiring, cable length and pull-ups |
| DS18B20 missing / timeout | Three-wire VDD/GND/DQ wiring, 3.3 V supply, cable/contact faults; on Rev 1.3/v2.0 power is switched only for conversions |
| Settings/Log cannot be opened | Enable Wi-Fi + web API and set an admin password in the portal; browser login user is `admin` |
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│   ├── config.h/.cpp        # Config struct, NVS load/save
│   ├── partition_check.h/.cpp  # Detects a missing "cfgdata" partition
│   ├── globals.h            # Shared live state between the modules
│   ├── sensors.h/.cpp       # Pins, pulse counters, ADC, sensor reads
│   ├── board_io.h/.cpp      # PCB v2.0: revision ID, AUX inputs, heater/fan, tacho, VE.Direct
│   ├── vedirect.h/.cpp      # Victron VE.Direct text-protocol parser (host-testable)
│   ├── payload.h            # Measurements struct + compact binary layout
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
